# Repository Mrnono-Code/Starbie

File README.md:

# Starbie
My custom starbie designed for hack club stardance

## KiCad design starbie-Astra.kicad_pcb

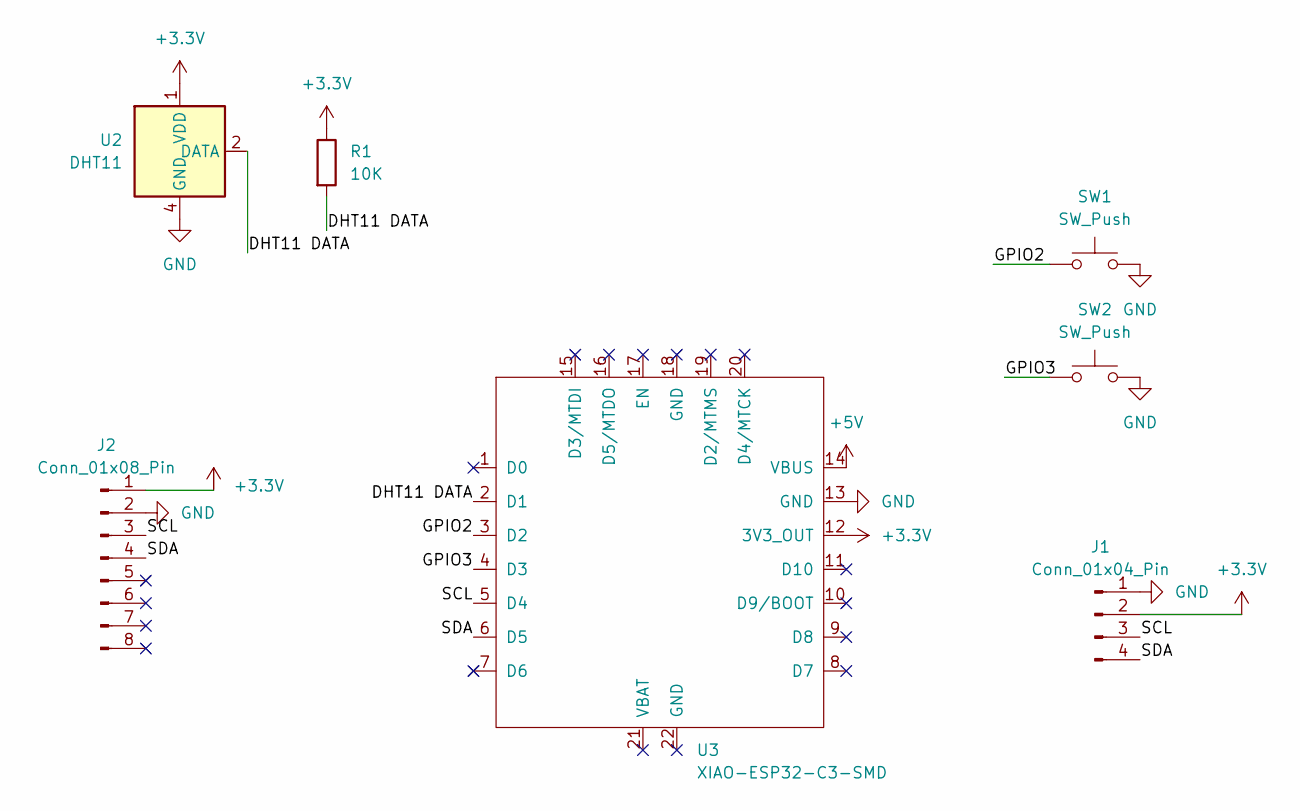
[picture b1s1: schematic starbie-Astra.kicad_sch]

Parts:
J1: Conn_01x04_Pin; Display_128x64_096_I2C
J2: Conn_01x08_Pin; PinHeader_1x08_P2.54mm_Vertical
R1: 10K; R_Axial_DIN0204_L3.6mm_D1.6mm_P7.62mm_Horizontal
SW1, SW2: SW_Push; SW_Cherry_MX_1.00u_PCB
U2: DHT11; Aosong_DHT11_5.5x12.0_P2.54mm
U3: XIAO-ESP32-C3-SMD; XIAO-ESP32-C6-DIP

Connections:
+3.3V: J1.2, J2.1, R1.1, U2.1 (VDD), U3.12 (3V3_OUT)
+5V: U3.14 (VBUS)
/DHT11 DATA: R1.2, U2.2 (DATA), U3.2 (D1)
/GPIO2: SW1.1, U3.3 (D2)
/GPIO3: SW2.1, U3.4 (D3)
/SCL: J1.3, J2.3, U3.5 (D4)
/SDA: J1.4, J2.4, U3.6 (D5)
GND: J1.1, J2.2, SW1.2, SW2.2, U2.4 (GND), U3.13 (GND)

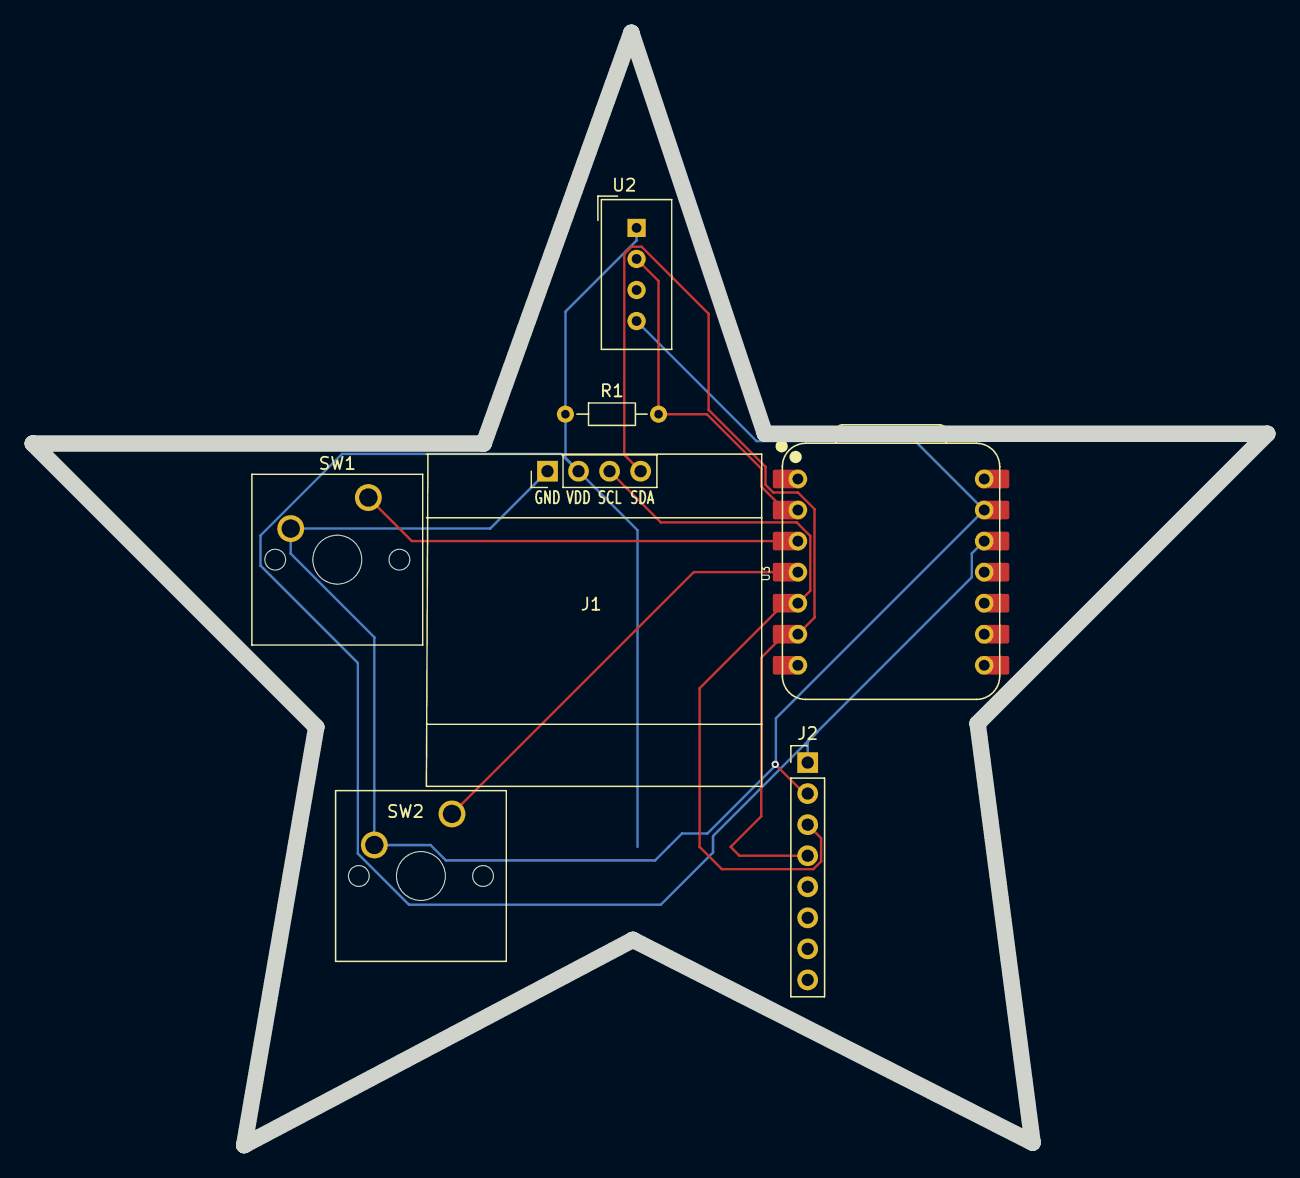
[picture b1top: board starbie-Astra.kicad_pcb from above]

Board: 2 copper layers, 101.0 x 91.0 mm, 7 parts (0 on the bottom side), 7 nets.
